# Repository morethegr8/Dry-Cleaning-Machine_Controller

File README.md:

View this project on [CADLAB.io](https://cadlab.io/project/1510). 

# Custom Firmware & Hardware for Dry Cleaning Machine [Fibrimatics, Italy]

This is a custom firmware for Atmel ATMEGA2560 controller based Control Board made for Dry Cleaning Machine Controller (Fibrimatics, Italy) . It uses the Atmel Studio and a number of 3rd party libraries.

## Contribute

There are several ways to contribute to Dry Cleaning Machine Controller development. You can contribute to the repository by doing:

* Pull requests (fixes, enhancements, new features... are very welcome)
* Documentation (I reckon I'm bad at it)
* Testing (filing issues or help resolving them, they take a lot of time and sometimes I don't have the required hardware to test them all)

And of course you can always buy me a beer, coffee, tea,... via the donation button below.

## Hardware

||
|---|
|||
|**Dry Cleaning Machine Controller**||

## License

Copyright (C) 2016-2018 by Amit More (@morethegr8)

This program is free software: you can redistribute it and/or modify it under the terms of the GNU General Public License as published by the Free Software Foundation, either version 3 of the License, or (at your option) any later version.

This program is distributed in the hope that it will be useful, but WITHOUT ANY WARRANTY; without even the implied warranty of MERCHANTABILITY or FITNESS FOR A PARTICULAR PURPOSE. See the GNU General Public License for more details.

You should have received a copy of the GNU General Public License along with this program. If not, see http://www.gnu.org/licenses/.

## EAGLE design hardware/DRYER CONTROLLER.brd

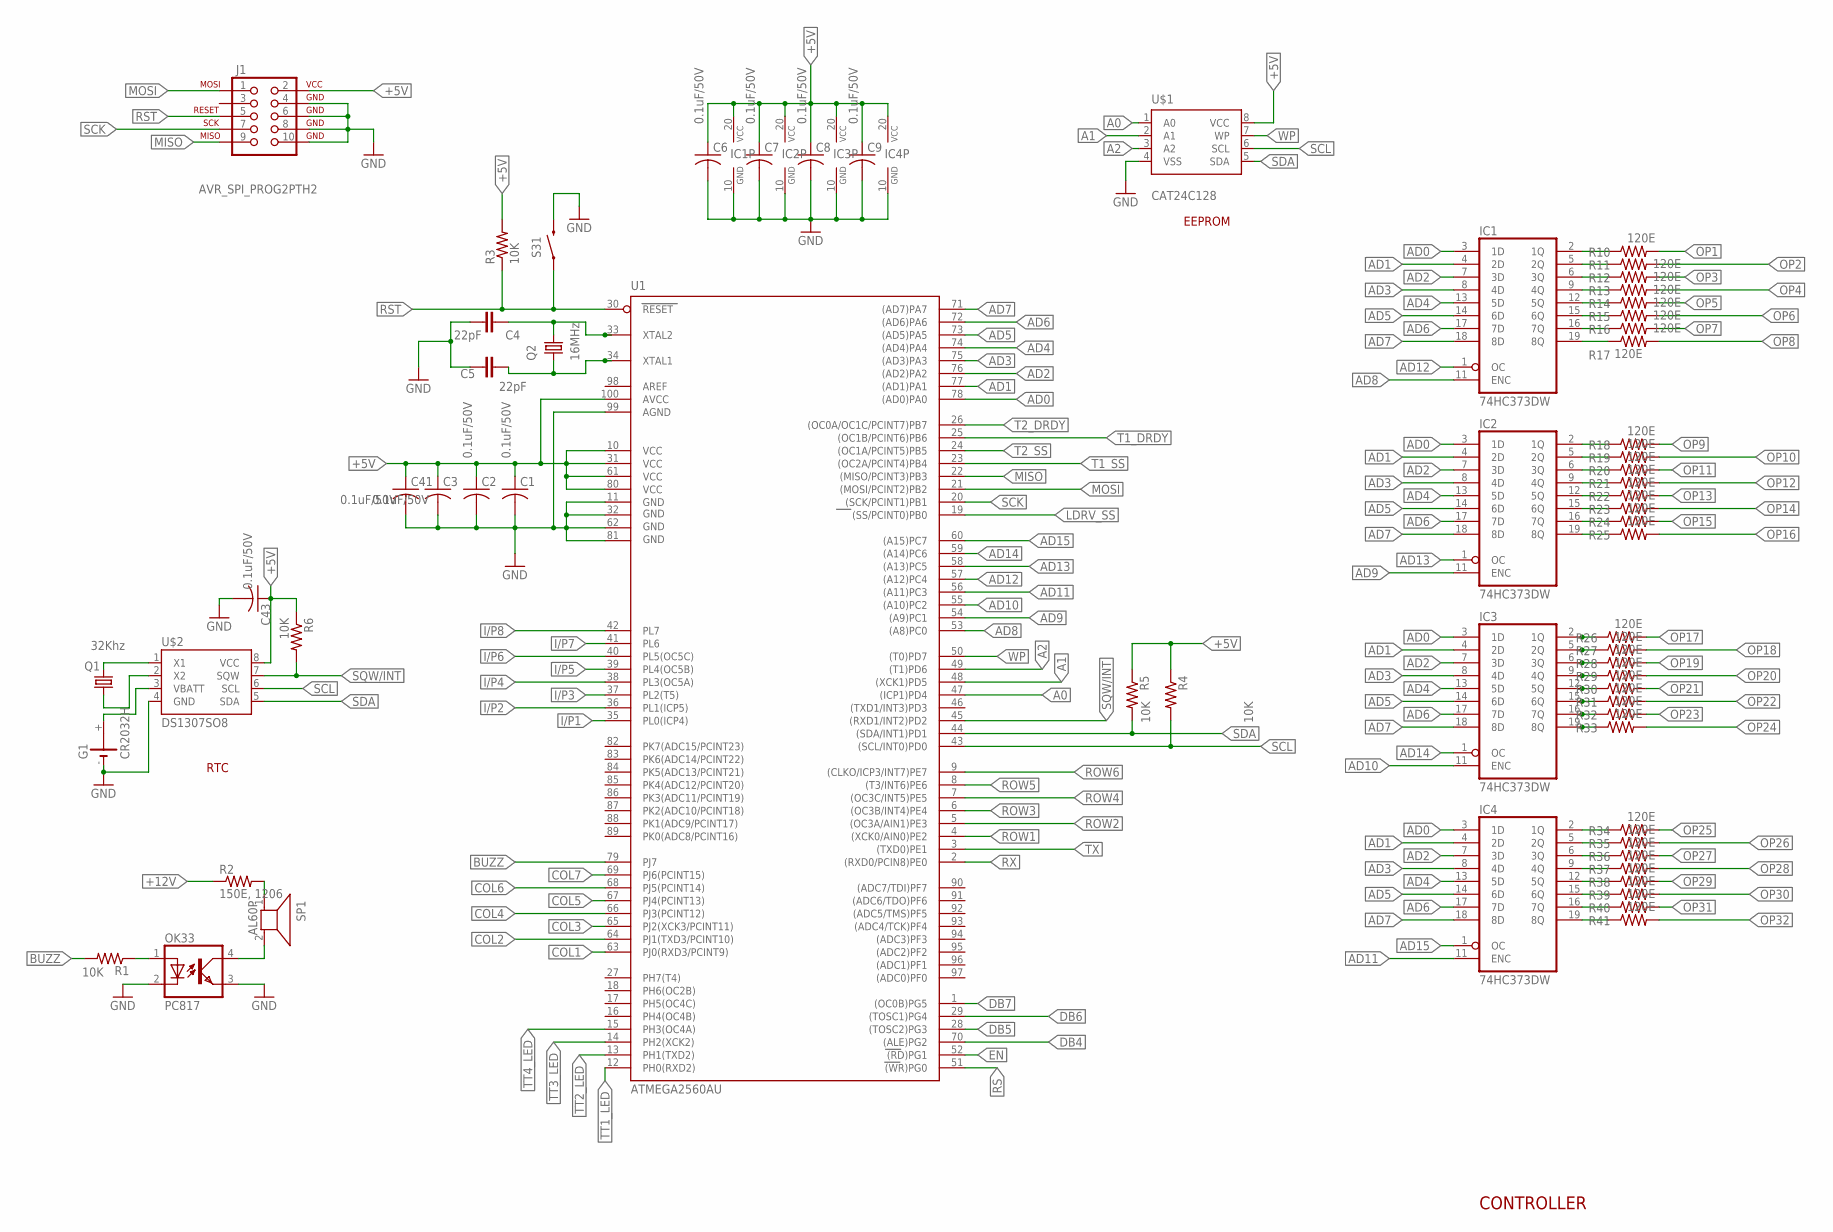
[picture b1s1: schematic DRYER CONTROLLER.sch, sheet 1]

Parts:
C1, C2, C3, C6, C7, C8, C9, C41, C43: 0.1uF/50V; C0805K
C4, C5: 22pF; 0805
G1: CR2032H
IC1, IC2, IC3, IC4: 74HC373DW; SO20W
J1: AVR_SPI_PROG2PTH2; 2X5-SHROUDED
OK33: PC817; DIL04
Q1: 32Khz; HC49/S
Q2: 16MHz; HC49/S
R1, R3, R4, R5, R6: 10K; R0805
R2: 150E, 1206; R1206
R10, R11, R12, R13, R14, R15, R16, R17, R18, R19, R20, R21, R22, R23, R24, R25, R26, R27, R28, R29, R30, R31, R32, R33, R34, R35, R36, R37, R38, R39, R40, R41: 120E; R0805
S31: SWITCH-MOMENTARY-2SMD-4; TACTILE_SWITCH_TALL
SP1: AL60P
U1: ATMEGA2560AU; TQFP100
U$1: CAT24C128; SOIC8
U$2: DS1307SO8; SO08

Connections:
+5V: C1.1, C2.1, C3.1, C6.1, C7.1, C8.1, C9.1, C41.1, C43.1, IC1.20 (VCC), IC2.20 (VCC), IC3.20 (VCC), IC4.20 (VCC), J1.2 (VCC), R3.2, R4.1, R5.1, R6.1, U1.10 (VCC), U1.31 (VCC1), U1.61 (VCC2), U1.80 (VCC3), U1.100 (AVCC), U$1.8 (VCC), U$2.8 (VCC); also elsewhere on the board
+12V: R2.1; also elsewhere on the board
A0: U1.47 ((ICP1)PD4), U$1.1 (A0)
A1: U1.48 ((XCK1)PD5), U$1.2 (A1)
A2: U1.49 ((T1)PD6), U$1.3 (A2)
AD0: IC1.3 (1D), IC2.3 (1D), IC3.3 (1D), IC4.3 (1D), U1.78 ((AD0)PA0)
AD1: IC1.4 (2D), IC2.4 (2D), IC3.4 (2D), IC4.4 (2D), U1.77 ((AD1)PA1)
AD2: IC1.7 (3D), IC2.7 (3D), IC3.7 (3D), IC4.7 (3D), U1.76 ((AD2)PA2)
AD3: IC1.8 (4D), IC2.8 (4D), IC3.8 (4D), IC4.8 (4D), U1.75 ((AD3)PA3)
AD4: IC1.13 (5D), IC2.13 (5D), IC3.13 (5D), IC4.13 (5D), U1.74 ((AD4)PA4)
AD5: IC1.14 (6D), IC2.14 (6D), IC3.14 (6D), IC4.14 (6D), U1.73 ((AD5)PA5)
AD6: IC1.17 (7D), IC2.17 (7D), IC3.17 (7D), IC4.17 (7D), U1.72 ((AD6)PA6)
AD7: IC1.18 (8D), IC2.18 (8D), IC3.18 (8D), IC4.18 (8D), U1.71 ((AD7)PA7)
AD8: IC1.11 (ENC), U1.53 ((A8)PC0)
AD9: IC2.11 (ENC), U1.54 ((A9)PC1)
AD10: IC3.11 (ENC), U1.55 ((A10)PC2)
AD11: IC4.11 (ENC), U1.56 ((A11)PC3)
AD12: IC1.1 (OC), U1.57 ((A12)PC4)
AD13: IC2.1 (OC), U1.58 ((A13)PC5)
AD14: IC3.1 (OC), U1.59 ((A14)PC6)
AD15: IC4.1 (OC), U1.60 ((A15)PC7)
BUZZ: R1.2, U1.79 (PJ7)
COL1: U1.63 (PJ0(RXD3/PCINT9)); also elsewhere on the board
COL2: U1.64 (PJ1(TXD3/PCINT10)); also elsewhere on the board
COL3: U1.65 (PJ2(XCK3/PCINT11)); also elsewhere on the board
COL4: U1.66 (PJ3(PCINT12)); also elsewhere on the board
COL5: U1.67 (PJ4(PCINT13)); also elsewhere on the board
COL6: U1.68 (PJ5(PCINT14)); also elsewhere on the board
COL7: U1.69 (PJ6(PCINT15)); also elsewhere on the board
DB4: U1.70 ((ALE)PG2); also elsewhere on the board
DB5: U1.28 ((TOSC2)PG3); also elsewhere on the board
DB6: U1.29 ((TOSC1)PG4); also elsewhere on the board
DB7: U1.1 ((OC0B)PG5); also elsewhere on the board
EN: U1.52 ((RD)PG1); also elsewhere on the board
GND: C1.2, C2.2, C3.2, C4.1, C5.1, C6.2, C7.2, C8.2, C9.2, C41.2, C43.2, G1.-, IC1.10 (GND), IC2.10 (GND), IC3.10 (GND), IC4.10 (GND), J1.4 (GND), J1.6 (GND), J1.8 (GND), J1.10 (GND), OK33.2 (C), OK33.3 (EMIT), S31.B2 (2), U1.11 (GND), U1.32 (GND1), U1.62 (GND2), U1.81 (GND3), U1.99 (AGND), U$1.4 (VSS), U$2.4 (GND); also elsewhere on the board
I/P1: U1.35 (PL0(ICP4)); also elsewhere on the board
I/P2: U1.36 (PL1(ICP5)); also elsewhere on the board
I/P3: U1.37 (PL2(T5)); also elsewhere on the board
I/P4: U1.38 (PL3(OC5A)); also elsewhere on the board
I/P5: U1.39 (PL4(OC5B)); also elsewhere on the board
I/P6: U1.40 (PL5(OC5C)); also elsewhere on the board
I/P7: U1.41 (PL6); also elsewhere on the board
I/P8: U1.42 (PL7); also elsewhere on the board
LDRV_SS: U1.19 ((SS/PCINT0)PB0); also elsewhere on the board
MISO: J1.9 (MISO), U1.22 ((MISO/PCINT3)PB3); also elsewhere on the board
MOSI: J1.1 (MOSI), U1.21 ((MOSI/PCINT2)PB2); also elsewhere on the board
unnamed: G1.+, U$2.3 (VBATT)
unnamed: Q1.2, U$2.2 (X2)
unnamed: Q1.1, U$2.1 (X1)
unnamed: C4.2, Q2.2, U1.33 (XTAL2)
unnamed: C5.2, Q2.1, U1.34 (XTAL1)
unnamed: IC1.2 (1Q), R10.1
unnamed: R2.2, SP1.1
unnamed: OK33.1 (A), R1.1
unnamed: IC1.5 (2Q), R11.1
unnamed: IC1.6 (3Q), R12.1
unnamed: IC1.9 (4Q), R13.1
unnamed: IC1.12 (5Q), R14.1
unnamed: IC1.15 (6Q), R15.1
unnamed: IC1.16 (7Q), R16.1
unnamed: IC1.19 (8Q), R17.1
unnamed: IC2.2 (1Q), R18.1
unnamed: IC2.5 (2Q), R19.1
unnamed: IC2.6 (3Q), R20.1
unnamed: IC2.9 (4Q), R21.1
unnamed: IC2.12 (5Q), R22.1
unnamed: IC2.15 (6Q), R23.1
unnamed: IC2.16 (7Q), R24.1
unnamed: IC2.19 (8Q), R25.1
unnamed: IC3.2 (1Q), R26.1
unnamed: IC3.5 (2Q), R27.1
unnamed: IC3.6 (3Q), R28.1
unnamed: IC3.9 (4Q), R29.1
unnamed: IC3.12 (5Q), R30.1
unnamed: IC3.15 (6Q), R31.1
unnamed: IC3.16 (7Q), R32.1
unnamed: IC4.19 (8Q), R41.1
unnamed: IC3.19 (8Q), R33.1
unnamed: IC4.16 (7Q), R40.1
unnamed: IC4.15 (6Q), R39.1
unnamed: IC4.12 (5Q), R38.1
unnamed: IC4.9 (4Q), R37.1
unnamed: IC4.6 (3Q), R36.1
unnamed: IC4.5 (2Q), R35.1
unnamed: IC4.2 (1Q), R34.1
unnamed: OK33.4 (COL), SP1.2
OP1: R10.2; also elsewhere on the board
OP2: R11.2; also elsewhere on the board
OP3: R12.2; also elsewhere on the board
OP4: R13.2; also elsewhere on the board
OP5: R14.2; also elsewhere on the board
OP6: R15.2; also elsewhere on the board
OP7: R16.2; also elsewhere on the board
OP8: R17.2; also elsewhere on the board
OP9: R18.2; also elsewhere on the board
OP10: R19.2; also elsewhere on the board
OP11: R20.2; also elsewhere on the board
OP12: R21.2; also elsewhere on the board
OP13: R22.2; also elsewhere on the board
OP14: R23.2; also elsewhere on the board
OP15: R24.2; also elsewhere on the board
OP16: R25.2; also elsewhere on the board
OP17: R26.2; also elsewhere on the board
OP18: R27.2; also elsewhere on the board
OP19: R28.2; also elsewhere on the board
OP20: R29.2; also elsewhere on the board
OP21: R30.2; also elsewhere on the board
OP22: R31.2; also elsewhere on the board
OP23: R32.2; also elsewhere on the board
OP24: R33.2; also elsewhere on the board
OP25: R34.2; also elsewhere on the board
OP26: R35.2; also elsewhere on the board
OP27: R36.2; also elsewhere on the board
OP28: R37.2; also elsewhere on the board
OP29: R38.2; also elsewhere on the board
OP30: R39.2; also elsewhere on the board
OP31: R40.2; also elsewhere on the board
OP32: R41.2; also elsewhere on the board
ROW1: U1.4 ((XCK0/AIN0)PE2); also elsewhere on the board
ROW2: U1.5 ((OC3A/AIN1)PE3); also elsewhere on the board
ROW3: U1.6 ((OC3B/INT4)PE4); also elsewhere on the board
ROW4: U1.7 ((OC3C/INT5)PE5); also elsewhere on the board
ROW5: U1.8 ((T3/INT6)PE6); also elsewhere on the board
ROW6: U1.9 ((CLKO/ICP3/INT7)PE7); also elsewhere on the board
RS: U1.51 ((WR)PG0); also elsewhere on the board
RST: J1.5 (RESET), R3.1, S31.A2 (1), U1.30 (RESET)
RX: U1.2 ((RXD0/PCIN8)PE0); also elsewhere on the board
SCK: J1.7 (SCK), U1.20 ((SCK/PCINT1)PB1); also elsewhere on the board
SCL: R4.2, U1.43 ((SCL/INT0)PD0), U$1.6 (SCL), U$2.6 (SCL)
SDA: R5.2, U1.44 ((SDA/INT1)PD1), U$1.5 (SDA), U$2.5 (SDA)
SQW/INT: R6.2, U1.45 ((RXD1/INT2)PD2), U$2.7 (SQW)
T1_DRDY: U1.25 ((OC1B/PCINT6)PB6); also elsewhere on the board
T1_SS: U1.23 ((OC2A/PCINT4)PB4); also elsewhere on the board
T2_DRDY: U1.26 ((OC0A/OC1C/PCINT7)PB7); also elsewhere on the board
T2_SS: U1.24 ((OC1A/PCINT5)PB5); also elsewhere on the board
TT1_LED: U1.12 (PH0(RXD2)); also elsewhere on the board
TT2_LED: U1.13 (PH1(TXD2)); also elsewhere on the board
TT3_LED: U1.14 (PH2(XCK2)); also elsewhere on the board
TT4_LED: U1.15 (PH3(OC4A)); also elsewhere on the board
TX: U1.3 ((TXD0)PE1); also elsewhere on the board
WP: U1.50 ((T0)PD7), U$1.7 (WP)

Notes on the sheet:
RTC
EEPROM
CONTROLLER

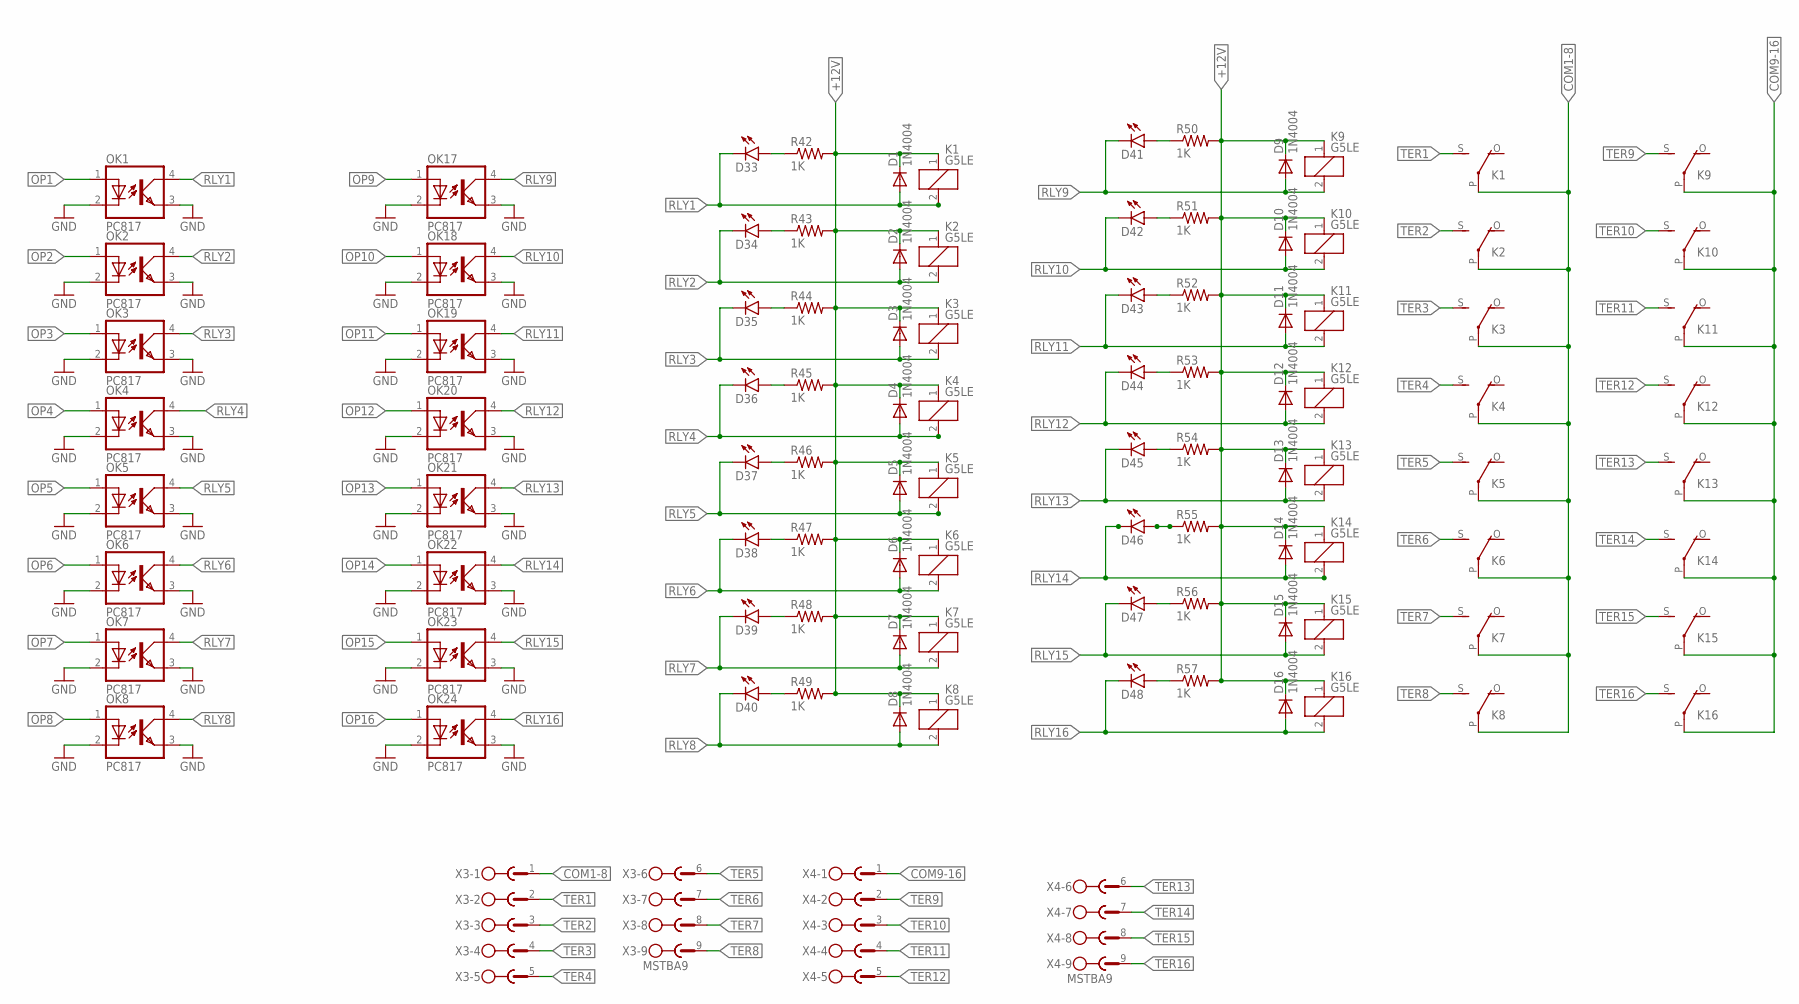
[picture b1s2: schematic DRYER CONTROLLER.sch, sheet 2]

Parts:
D1, D2, D3, D4, D5, D6, D7, D8, D9, D10, D11, D12, D13, D14, D15, D16: 1N4004; DO41-10
D33, D34, D35, D36, D37, D38, D39, D40, D41, D42, D43, D44, D45, D46, D47, D48: LED1206; LED-1206
K1, K2, K3, K4, K5, K6, K7, K8, K9, K10, K11, K12, K13, K14, K15, K16: G5LE
OK1, OK2, OK3, OK4, OK5, OK6, OK7, OK8, OK17, OK18, OK19, OK20, OK21, OK22, OK23, OK24: PC817; DIL04
R42, R43, R44, R45, R46, R47, R48, R49, R50, R51, R52, R53, R54, R55, R56, R57: 1K; R0805
X3, X4: MSTBA9

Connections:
+12V: D1.C, D2.C, D3.C, D4.C, D5.C, D6.C, D7.C, D8.C, D9.C, D10.C, D11.C, D12.C, D13.C, D14.C, D15.C, D16.C, K1.1, K2.1, K3.1, K4.1, K5.1, K6.1, K7.1, K8.1, K9.1, K10.1, K11.1, K12.1, K13.1, K14.1, K15.1, K16.1, R42.2, R43.2, R44.2, R45.2, R46.2, R47.2, R48.2, R49.2, R50.2, R51.2, R52.2, R53.2, R54.2, R55.2, R56.2, R57.2; also elsewhere on the board
COM1-8: K1.P, K2.P, K3.P, K4.P, K5.P, K6.P, K7.P, K8.P, X3.1
COM9-16: K9.P, K10.P, K11.P, K12.P, K13.P, K14.P, K15.P, K16.P, X4.1
GND: OK1.2 (C), OK1.3 (EMIT), OK2.2 (C), OK2.3 (EMIT), OK3.2 (C), OK3.3 (EMIT), OK4.2 (C), OK4.3 (EMIT), OK5.2 (C), OK5.3 (EMIT), OK6.2 (C), OK6.3 (EMIT), OK7.2 (C), OK7.3 (EMIT), OK8.2 (C), OK8.3 (EMIT), OK17.2 (C), OK17.3 (EMIT), OK18.2 (C), OK18.3 (EMIT), OK19.2 (C), OK19.3 (EMIT), OK20.2 (C), OK20.3 (EMIT), OK21.2 (C), OK21.3 (EMIT), OK22.2 (C), OK22.3 (EMIT), OK23.2 (C), OK23.3 (EMIT), OK24.2 (C), OK24.3 (EMIT); also elsewhere on the board
unnamed: D33.A, R42.1
unnamed: D34.A, R43.1
unnamed: D35.A, R44.1
unnamed: D36.A, R45.1
unnamed: D37.A, R46.1
unnamed: D38.A, R47.1
unnamed: D39.A, R48.1
unnamed: D40.A, R49.1
unnamed: D41.A, R50.1
unnamed: D42.A, R51.1
unnamed: D43.A, R52.1
unnamed: D44.A, R53.1
unnamed: D45.A, R54.1
unnamed: D47.A, R56.1
unnamed: D48.A, R57.1
unnamed: D46.A, R55.1
OP1: OK1.1 (A); also elsewhere on the board
OP2: OK2.1 (A); also elsewhere on the board
OP3: OK3.1 (A); also elsewhere on the board
OP4: OK4.1 (A); also elsewhere on the board
OP5: OK5.1 (A); also elsewhere on the board
OP6: OK6.1 (A); also elsewhere on the board
OP7: OK7.1 (A); also elsewhere on the board
OP8: OK8.1 (A); also elsewhere on the board
OP9: OK17.1 (A); also elsewhere on the board
OP10: OK18.1 (A); also elsewhere on the board
OP11: OK19.1 (A); also elsewhere on the board
OP12: OK20.1 (A); also elsewhere on the board
OP13: OK21.1 (A); also elsewhere on the board
OP14: OK22.1 (A); also elsewhere on the board
OP15: OK23.1 (A); also elsewhere on the board
OP16: OK24.1 (A); also elsewhere on the board
RLY1: D1.A, D33.C, K1.2, OK1.4 (COL); also elsewhere on the board
RLY2: D2.A, D34.C, K2.2, OK2.4 (COL); also elsewhere on the board
RLY3: D3.A, D35.C, K3.2, OK3.4 (COL); also elsewhere on the board
RLY4: D4.A, D36.C, K4.2, OK4.4 (COL); also elsewhere on the board
RLY5: D5.A, D37.C, K5.2, OK5.4 (COL); also elsewhere on the board
RLY6: D6.A, D38.C, K6.2, OK6.4 (COL); also elsewhere on the board
RLY7: D7.A, D39.C, K7.2, OK7.4 (COL); also elsewhere on the board
RLY8: D8.A, D40.C, K8.2, OK8.4 (COL); also elsewhere on the board
RLY9: D9.A, D41.C, K9.2, OK17.4 (COL); also elsewhere on the board
RLY10: D10.A, D42.C, K10.2, OK18.4 (COL); also elsewhere on the board
RLY11: D11.A, D43.C, K11.2, OK19.4 (COL); also elsewhere on the board
RLY12: D12.A, D44.C, K12.2, OK20.4 (COL); also elsewhere on the board
RLY13: D13.A, D45.C, K13.2, OK21.4 (COL); also elsewhere on the board
RLY14: D14.A, D46.C, K14.2, OK22.4 (COL); also elsewhere on the board
RLY15: D15.A, D47.C, K15.2, OK23.4 (COL); also elsewhere on the board
RLY16: D16.A, D48.C, K16.2, OK24.4 (COL); also elsewhere on the board
TER1: K1.S, X3.2
TER2: K2.S, X3.3
TER3: K3.S, X3.4
TER4: K4.S, X3.5
TER5: K5.S, X3.6
TER6: K6.S, X3.7
TER7: K7.S, X3.8
TER8: K8.S, X3.9
TER9: K9.S, X4.2
TER10: K10.S, X4.3
TER11: K11.S, X4.4
TER12: K12.S, X4.5
TER13: K13.S, X4.6
TER14: K14.S, X4.7
TER15: K15.S, X4.8
TER16: K16.S, X4.9

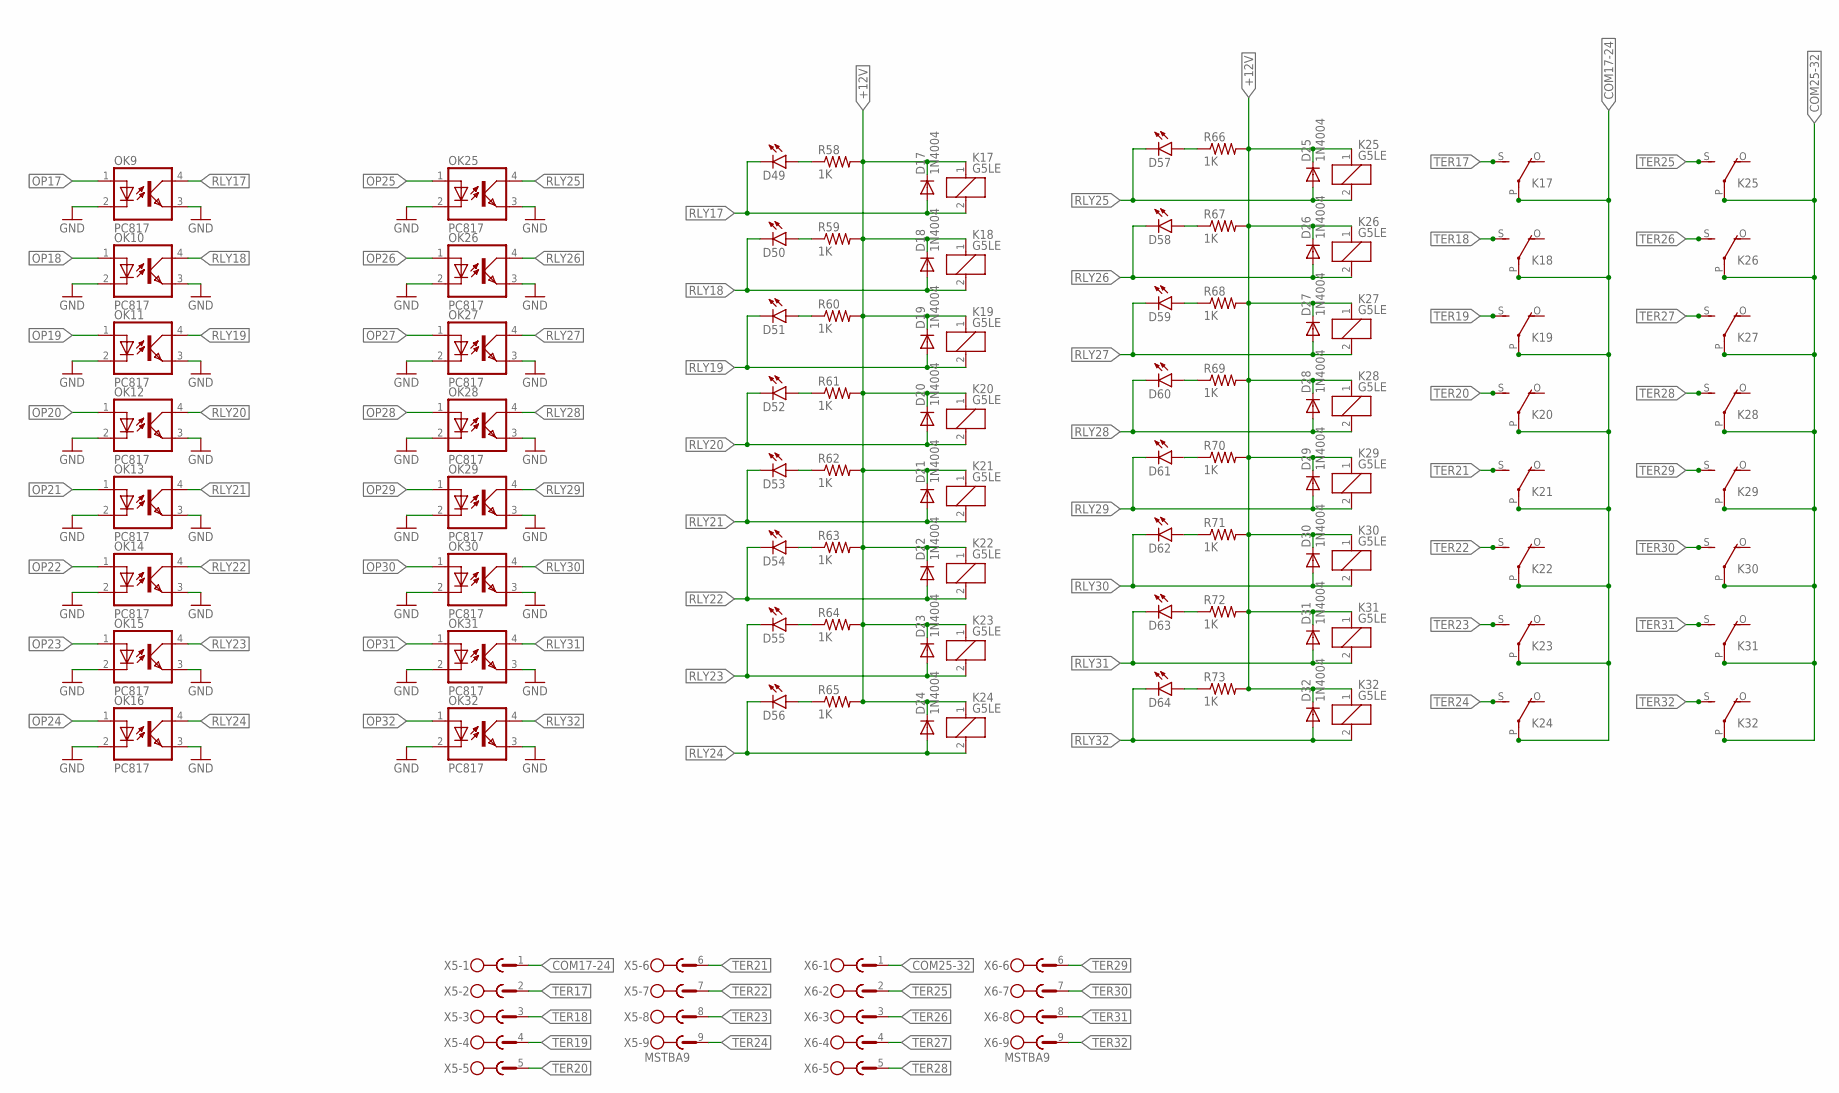
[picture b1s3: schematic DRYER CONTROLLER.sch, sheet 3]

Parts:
D17, D18, D19, D20, D21, D22, D23, D24, D25, D26, D27, D28, D29, D30, D31, D32: 1N4004; DO41-10
D49, D50, D51, D52, D53, D54, D55, D56, D57, D58, D59, D60, D61, D62, D63, D64: LED1206; LED-1206
K17, K18, K19, K20, K21, K22, K23, K24, K25, K26, K27, K28, K29, K30, K31, K32: G5LE
OK9, OK10, OK11, OK12, OK13, OK14, OK15, OK16, OK25, OK26, OK27, OK28, OK29, OK30, OK31, OK32: PC817; DIL04
R58, R59, R60, R61, R62, R63, R64, R65, R66, R67, R68, R69, R70, R71, R72, R73: 1K; R0805
X5, X6: MSTBA9

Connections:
+12V: D17.C, D18.C, D19.C, D20.C, D21.C, D22.C, D23.C, D24.C, D25.C, D26.C, D27.C, D28.C, D29.C, D30.C, D31.C, D32.C, K17.1, K18.1, K19.1, K20.1, K21.1, K22.1, K23.1, K24.1, K25.1, K26.1, K27.1, K28.1, K29.1, K30.1, K31.1, K32.1, R58.2, R59.2, R60.2, R61.2, R62.2, R63.2, R64.2, R65.2, R66.2, R67.2, R68.2, R69.2, R70.2, R71.2, R72.2, R73.2; also elsewhere on the board
COM17-24: K17.P, K18.P, K19.P, K20.P, K21.P, K22.P, K23.P, K24.P, X5.1
COM25-32: K25.P, K26.P, K27.P, K28.P, K29.P, K30.P, K31.P, K32.P, X6.1
GND: OK9.2 (C), OK9.3 (EMIT), OK10.2 (C), OK10.3 (EMIT), OK11.2 (C), OK11.3 (EMIT), OK12.2 (C), OK12.3 (EMIT), OK13.2 (C), OK13.3 (EMIT), OK14.2 (C), OK14.3 (EMIT), OK15.2 (C), OK15.3 (EMIT), OK16.2 (C), OK16.3 (EMIT), OK25.2 (C), OK25.3 (EMIT), OK26.2 (C), OK26.3 (EMIT), OK27.2 (C), OK27.3 (EMIT), OK28.2 (C), OK28.3 (EMIT), OK29.2 (C), OK29.3 (EMIT), OK30.2 (C), OK30.3 (EMIT), OK31.2 (C), OK31.3 (EMIT), OK32.2 (C), OK32.3 (EMIT); also elsewhere on the board
unnamed: D49.A, R58.1
unnamed: D50.A, R59.1
unnamed: D51.A, R60.1
unnamed: D52.A, R61.1
unnamed: D53.A, R62.1
unnamed: D54.A, R63.1
unnamed: D55.A, R64.1
unnamed: D56.A, R65.1
unnamed: D57.A, R66.1
unnamed: D58.A, R67.1
unnamed: D59.A, R68.1
unnamed: D60.A, R69.1
unnamed: D61.A, R70.1
unnamed: D62.A, R71.1
unnamed: D63.A, R72.1
unnamed: D64.A, R73.1
OP17: OK9.1 (A); also elsewhere on the board
OP18: OK10.1 (A); also elsewhere on the board
OP19: OK11.1 (A); also elsewhere on the board
OP20: OK12.1 (A); also elsewhere on the board
OP21: OK13.1 (A); also elsewhere on the board
OP22: OK14.1 (A); also elsewhere on the board
OP23: OK15.1 (A); also elsewhere on the board
OP24: OK16.1 (A); also elsewhere on the board
OP25: OK25.1 (A); also elsewhere on the board
OP26: OK26.1 (A); also elsewhere on the board
OP27: OK27.1 (A); also elsewhere on the board
OP28: OK28.1 (A); also elsewhere on the board
OP29: OK29.1 (A); also elsewhere on the board
OP30: OK30.1 (A); also elsewhere on the board
OP31: OK31.1 (A); also elsewhere on the board
OP32: OK32.1 (A); also elsewhere on the board
RLY17: D17.A, D49.C, K17.2, OK9.4 (COL); also elsewhere on the board
RLY18: D18.A, D50.C, K18.2, OK10.4 (COL); also elsewhere on the board
RLY19: D19.A, D51.C, K19.2, OK11.4 (COL); also elsewhere on the board
RLY20: D20.A, D52.C, K20.2, OK12.4 (COL); also elsewhere on the board
RLY21: D21.A, D53.C, K21.2, OK13.4 (COL); also elsewhere on the board
RLY22: D22.A, D54.C, K22.2, OK14.4 (COL); also elsewhere on the board
RLY23: D23.A, D55.C, K23.2, OK15.4 (COL); also elsewhere on the board
RLY24: D24.A, D56.C, K24.2, OK16.4 (COL); also elsewhere on the board
RLY25: D25.A, D57.C, K25.2, OK25.4 (COL); also elsewhere on the board
RLY26: D26.A, D58.C, K26.2, OK26.4 (COL); also elsewhere on the board
RLY27: D27.A, D59.C, K27.2, OK27.4 (COL); also elsewhere on the board
RLY28: D28.A, D60.C, K28.2, OK28.4 (COL); also elsewhere on the board
RLY29: D29.A, D61.C, K29.2, OK29.4 (COL); also elsewhere on the board
RLY30: D30.A, D62.C, K30.2, OK30.4 (COL); also elsewhere on the board
RLY31: D31.A, D63.C, K31.2, OK31.4 (COL); also elsewhere on the board
RLY32: D32.A, D64.C, K32.2, OK32.4 (COL); also elsewhere on the board
TER17: K17.S, X5.2
TER18: K18.S, X5.3
TER19: K19.S, X5.4
TER20: K20.S, X5.5
TER21: K21.S, X5.6
TER22: K22.S, X5.7
TER23: K23.S, X5.8
TER24: K24.S, X5.9
TER25: K25.S, X6.2
TER26: K26.S, X6.3
TER27: K27.S, X6.4
TER28: K28.S, X6.5
TER29: K29.S, X6.6
TER30: K30.S, X6.7
TER31: K31.S, X6.8
TER32: K32.S, X6.9

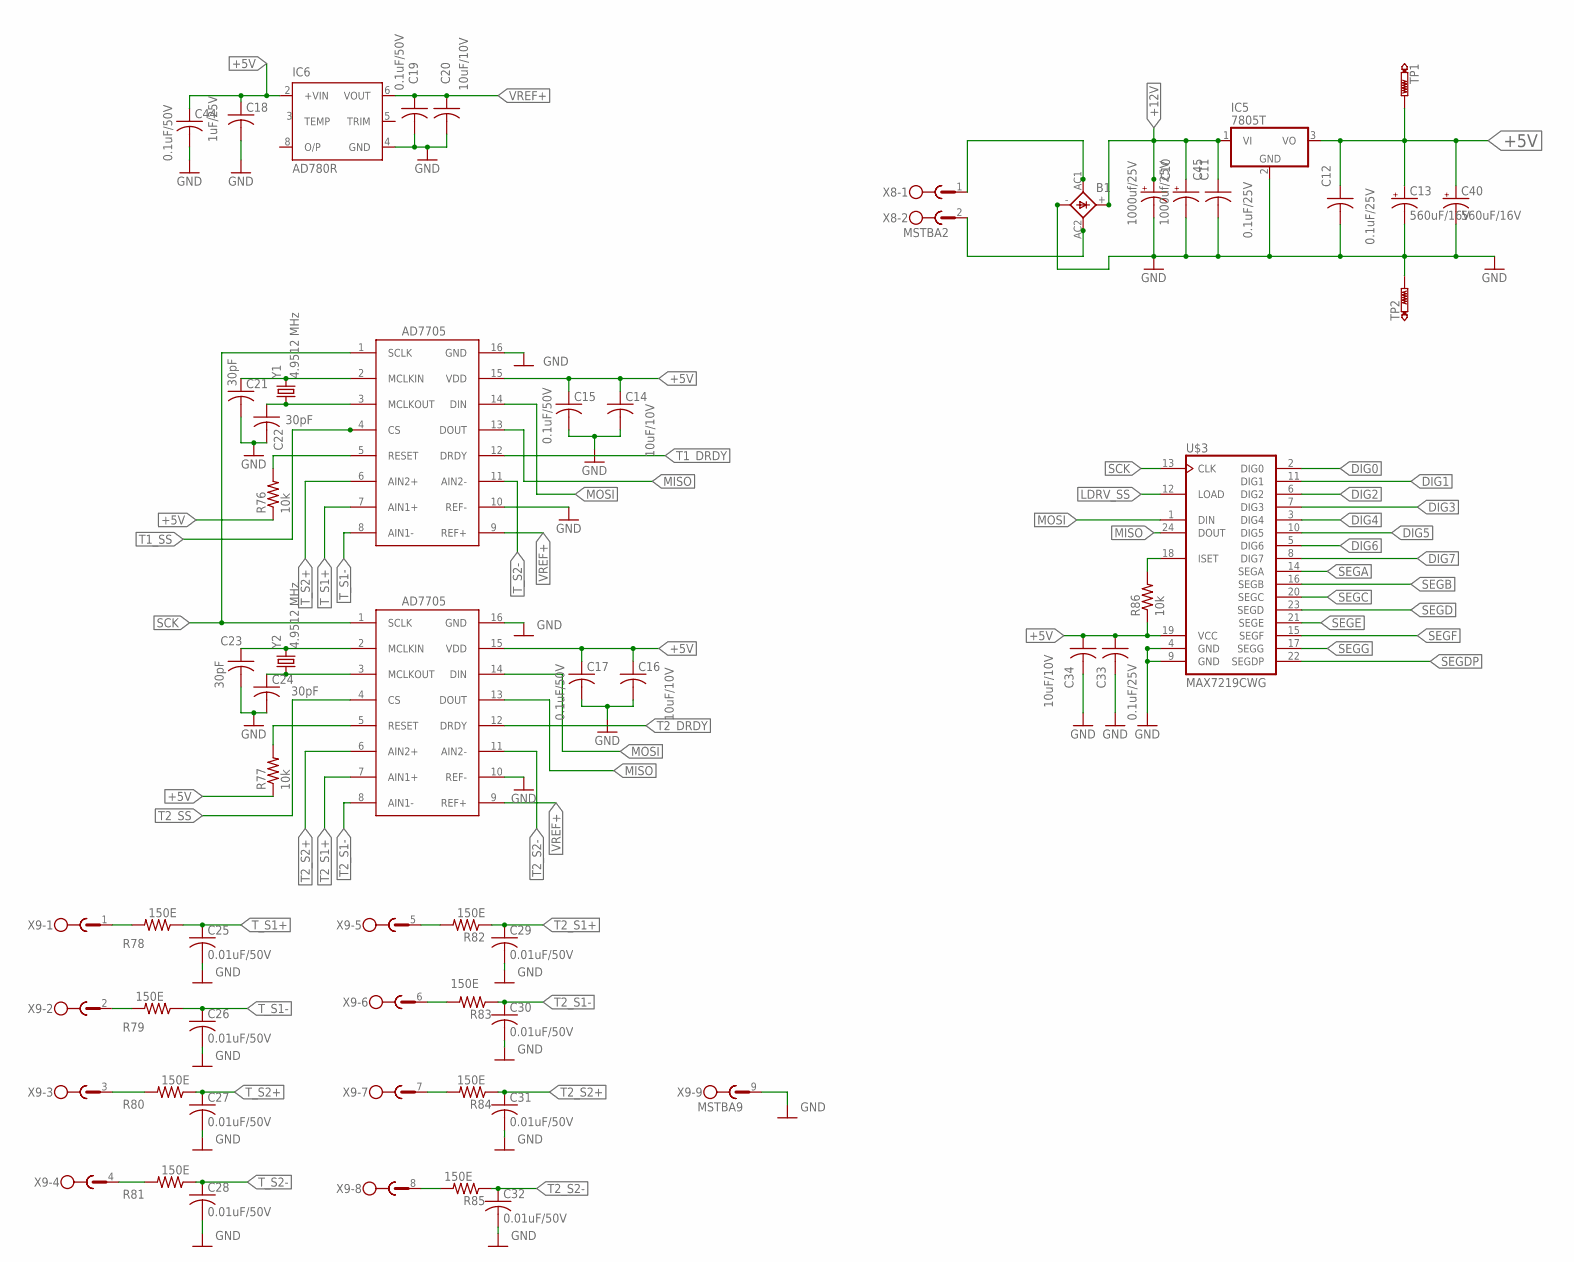
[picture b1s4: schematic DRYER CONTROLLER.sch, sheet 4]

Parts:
B1: 2KBP
C10, C45: 1000uf/25V; CPOL-RADIAL-1000UF-25V-KIT
C11, C12, C33: 0.1uF/25V; C0805K
C13, C40: 560uF/16V; E5-8,5
C14, C16, C20, C34: 10uF/10V; C0805K
C15, C17, C19, C44: 0.1uF/50V; C0805K
C18: 1uF/25V; C0805K
C21, C22, C23, C24: 30pF; C0603K
C25, C26, C27, C28, C29, C30, C31, C32: 0.01uF/50V; C0603
IC5: 7805T; TO220H
IC6: AD780R; SO8
R76, R77, R86: 10k; R0805
R78, R79, R80, R81, R82, R83, R84, R85: 150E; R0805
TP1, TP2: PTR1B2,54; B2,54
U$3: MAX7219CWG; SO24L
U$4, U$5: AD7705; SO-16W
X8: MSTBA2
X9: MSTBA9
Y1, Y2: 4.9512 MHz; HC49U-V

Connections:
+5V: C12.1, C13.+, C14.1, C15.1, C16.1, C17.1, C18.1, C33.1, C34.1, C40.+, C44.1, IC5.3 (VO), IC6.2 (+VIN), R76.1, R77.1, R86.1, TP1.TP, U$3.19 (VCC), U$4.15 (VDD), U$5.15 (VDD); also elsewhere on the board
+12V: B1.+, C10.+, C11.1, C45.+, IC5.1 (VI); also elsewhere on the board
DIG0: U$3.2 (DIG0); also elsewhere on the board
DIG1: U$3.11 (DIG1); also elsewhere on the board
DIG2: U$3.6 (DIG2); also elsewhere on the board
DIG3: U$3.7 (DIG3); also elsewhere on the board
DIG4: U$3.3 (DIG4)
DIG5: U$3.10 (DIG5)
DIG6: U$3.5 (DIG6)
DIG7: U$3.8 (DIG7)
GND: B1.-, C10.-, C11.2, C12.2, C13.-, C14.2, C15.2, C16.2, C17.2, C18.2, C19.2, C20.2, C21.2, C22.2, C23.2, C24.2, C25.2, C26.2, C27.2, C28.2, C29.2, C30.2, C31.2, C32.2, C33.2, C34.2, C40.-, C44.2, C45.-, IC5.2 (GND), IC6.4 (GND), TP2.TP, U$3.4 (GND), U$3.9 (GND), U$4.10 (REF-), U$4.16 (GND), U$5.10 (REF-), U$5.16 (GND), X9.9; also elsewhere on the board
LDRV_SS: U$3.12 (LOAD); also elsewhere on the board
MISO: U$3.24 (DOUT), U$4.13 (DOUT), U$5.13 (DOUT); also elsewhere on the board
MOSI: U$3.1 (DIN), U$4.14 (DIN), U$5.14 (DIN); also elsewhere on the board
unnamed: B1.AC1, X8.1
unnamed: B1.AC2, X8.2
unnamed: R78.2, X9.1
unnamed: C21.1, U$4.2 (MCLKIN), Y1.2
unnamed: C22.1, U$4.3 (MCLKOUT), Y1.1
unnamed: C23.1, U$5.2 (MCLKIN), Y2.2
unnamed: C24.1, U$5.3 (MCLKOUT), Y2.1
unnamed: R76.2, U$4.5 (RESET)
unnamed: R77.2, U$5.5 (RESET)
unnamed: R79.2, X9.2
unnamed: R80.2, X9.3
unnamed: R81.2, X9.4
unnamed: R82.2, X9.5
unnamed: R83.2, X9.6
unnamed: R84.2, X9.7
unnamed: R85.2, X9.8
unnamed: R86.2, U$3.18 (ISET)
SCK: U$3.13 (CLK), U$4.1 (SCLK), U$5.1 (SCLK); also elsewhere on the board
SEGA: U$3.14 (SEGA); also elsewhere on the board
SEGB: U$3.16 (SEGB); also elsewhere on the board
SEGC: U$3.20 (SEGC); also elsewhere on the board
SEGD: U$3.23 (SEGD); also elsewhere on the board
SEGDP: U$3.22 (SEGDP); also elsewhere on the board
SEGE: U$3.21 (SEGE); also elsewhere on the board
SEGF: U$3.15 (SEGF); also elsewhere on the board
SEGG: U$3.17 (SEGG); also elsewhere on the board
T1_DRDY: U$4.12 (DRDY); also elsewhere on the board
T1_SS: U$4.4 (CS); also elsewhere on the board
T2_DRDY: U$5.12 (DRDY); also elsewhere on the board
T2_S1+: C29.1, R82.1, U$5.7 (AIN1+)
T2_S1-: C30.1, R83.1, U$5.8 (AIN1-)
T2_S2+: C31.1, R84.1, U$5.6 (AIN2+)
T2_S2-: C32.1, R85.1, U$5.11 (AIN2-)
T2_SS: U$5.4 (CS); also elsewhere on the board
T_S1+: C25.1, R78.1, U$4.7 (AIN1+)
T_S1-: C26.1, R79.1, U$4.8 (AIN1-)
T_S2+: C27.1, R80.1, U$4.6 (AIN2+)
T_S2-: C28.1, R81.1, U$4.11 (AIN2-)
VREF+: C19.1, C20.1, IC6.6 (VOUT), U$4.9 (REF+), U$5.9 (REF+)

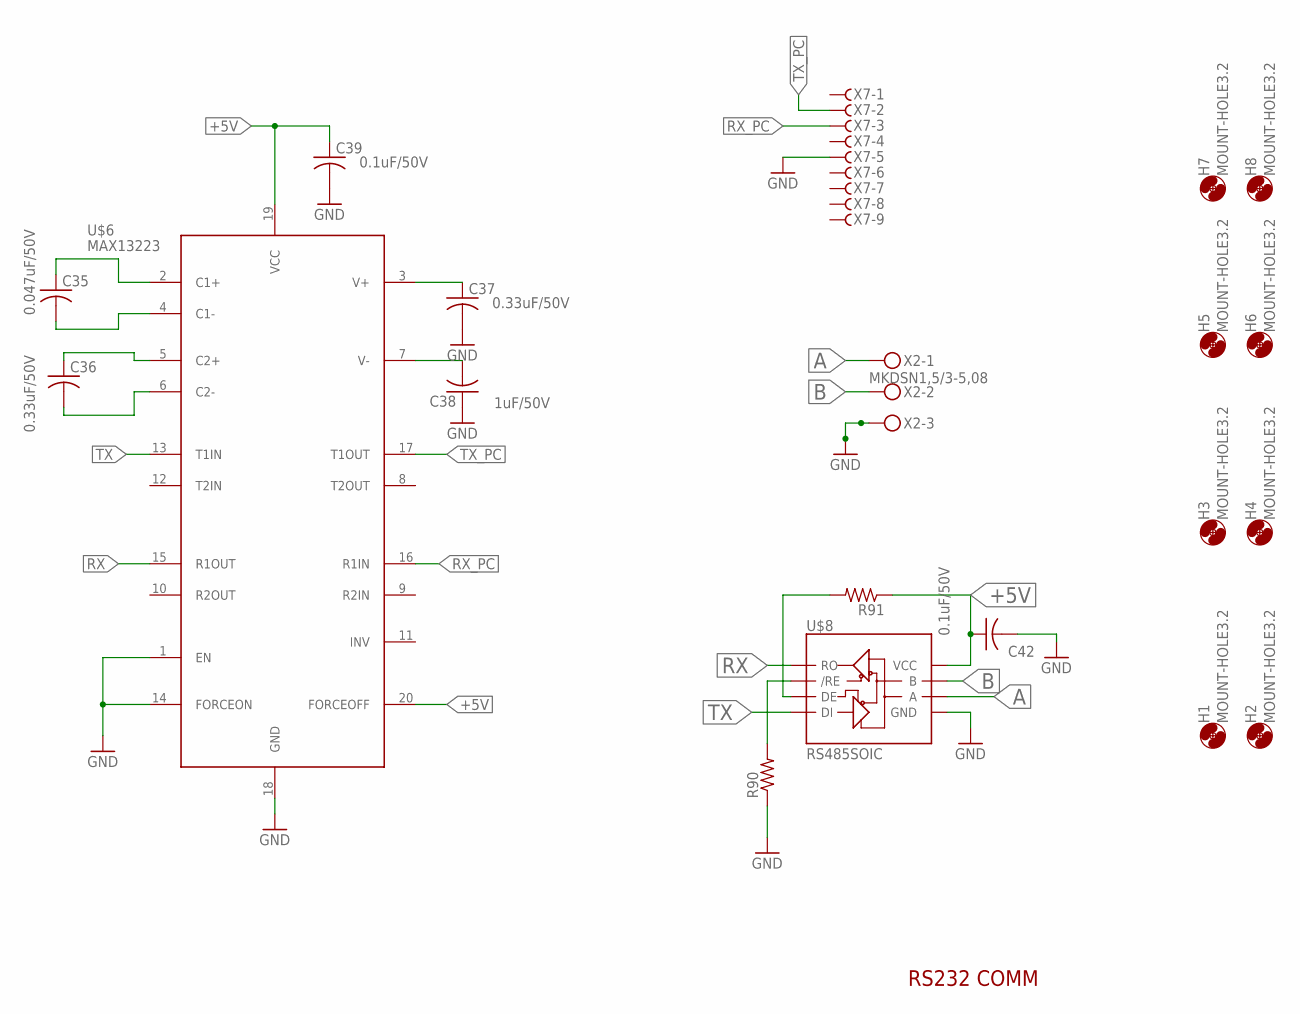
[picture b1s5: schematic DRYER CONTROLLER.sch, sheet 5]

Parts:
C35: 0.047uF/50V; C0805K
C36, C37: 0.33uF/50V; C0805K
C38: 1uF/50V; C0805K
C39, C42: 0.1uF/50V; C0805K
H1, H2, H3, H4, H5, H6, H7, H8: MOUNT-HOLE3.2; 3,2
R90, R91: R-US_R0805; R0805
U$6: MAX13223; TSSOP20
U$8: RS485SOIC; SO08
X2: MKDSN1,5/3-5,08
X7: F09.590S; 177-009-FEMALE

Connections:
+5V: C39.1, C42.1, R91.1, U$6.19 (VCC), U$6.20 (FORCEOFF), U$8.8 (VCC); also elsewhere on the board
A: U$8.6 (A), X2.1
B: U$8.7 (B), X2.2
GND: C37.2, C38.1, C39.2, C42.2, R90.1, U$6.1 (EN), U$6.14 (FORCEON), U$6.18 (GND), U$8.5 (GND), X2.3, X7.5; also elsewhere on the board
unnamed: C35.1, U$6.2 (C1+)
unnamed: C35.2, U$6.4 (C1-)
unnamed: C36.1, U$6.5 (C2+)
unnamed: C36.2, U$6.6 (C2-)
unnamed: C37.1, U$6.3 (V+)
unnamed: C38.2, U$6.7 (V-)
unnamed: R91.2, U$8.3 (DE)
unnamed: R90.2, U$8.2 (/RE)
RX: U$6.15 (R1OUT), U$8.1 (RO); also elsewhere on the board
RX_PC: U$6.16 (R1IN), X7.3
TX: U$6.13 (T1IN), U$8.4 (DI); also elsewhere on the board
TX_PC: U$6.17 (T1OUT), X7.2

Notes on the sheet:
RS232 COMM

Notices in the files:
parts and their libraries:
SparkFun-DigitalIC: Licensing: Creative Commons ShareAlike 4.0 International - https://creativecommons.org/licenses/by-sa/4.0
Wire_to_Board_Connectors_rev15d: Copyright: Würth Elektronik
